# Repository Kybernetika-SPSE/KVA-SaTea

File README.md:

# KVA-SaTea
Model malé vesmírné sondy pro výuku

## Dokumentace a výrobní podklady

 - Schéma [zde](scheme.pdf)
 - Seznam součástek pro osazování - [html](bom/ibom.html), [csv](bom/BOM-SaTea.csv)
 - Archivované gerber soubory pro výrobu [zde](production/SaTea_-_small_teachy_satellite_4.zip)
 - 

## Licence

Projekt je volně šířitelný pod MIT licencí [zde](LICENSE)

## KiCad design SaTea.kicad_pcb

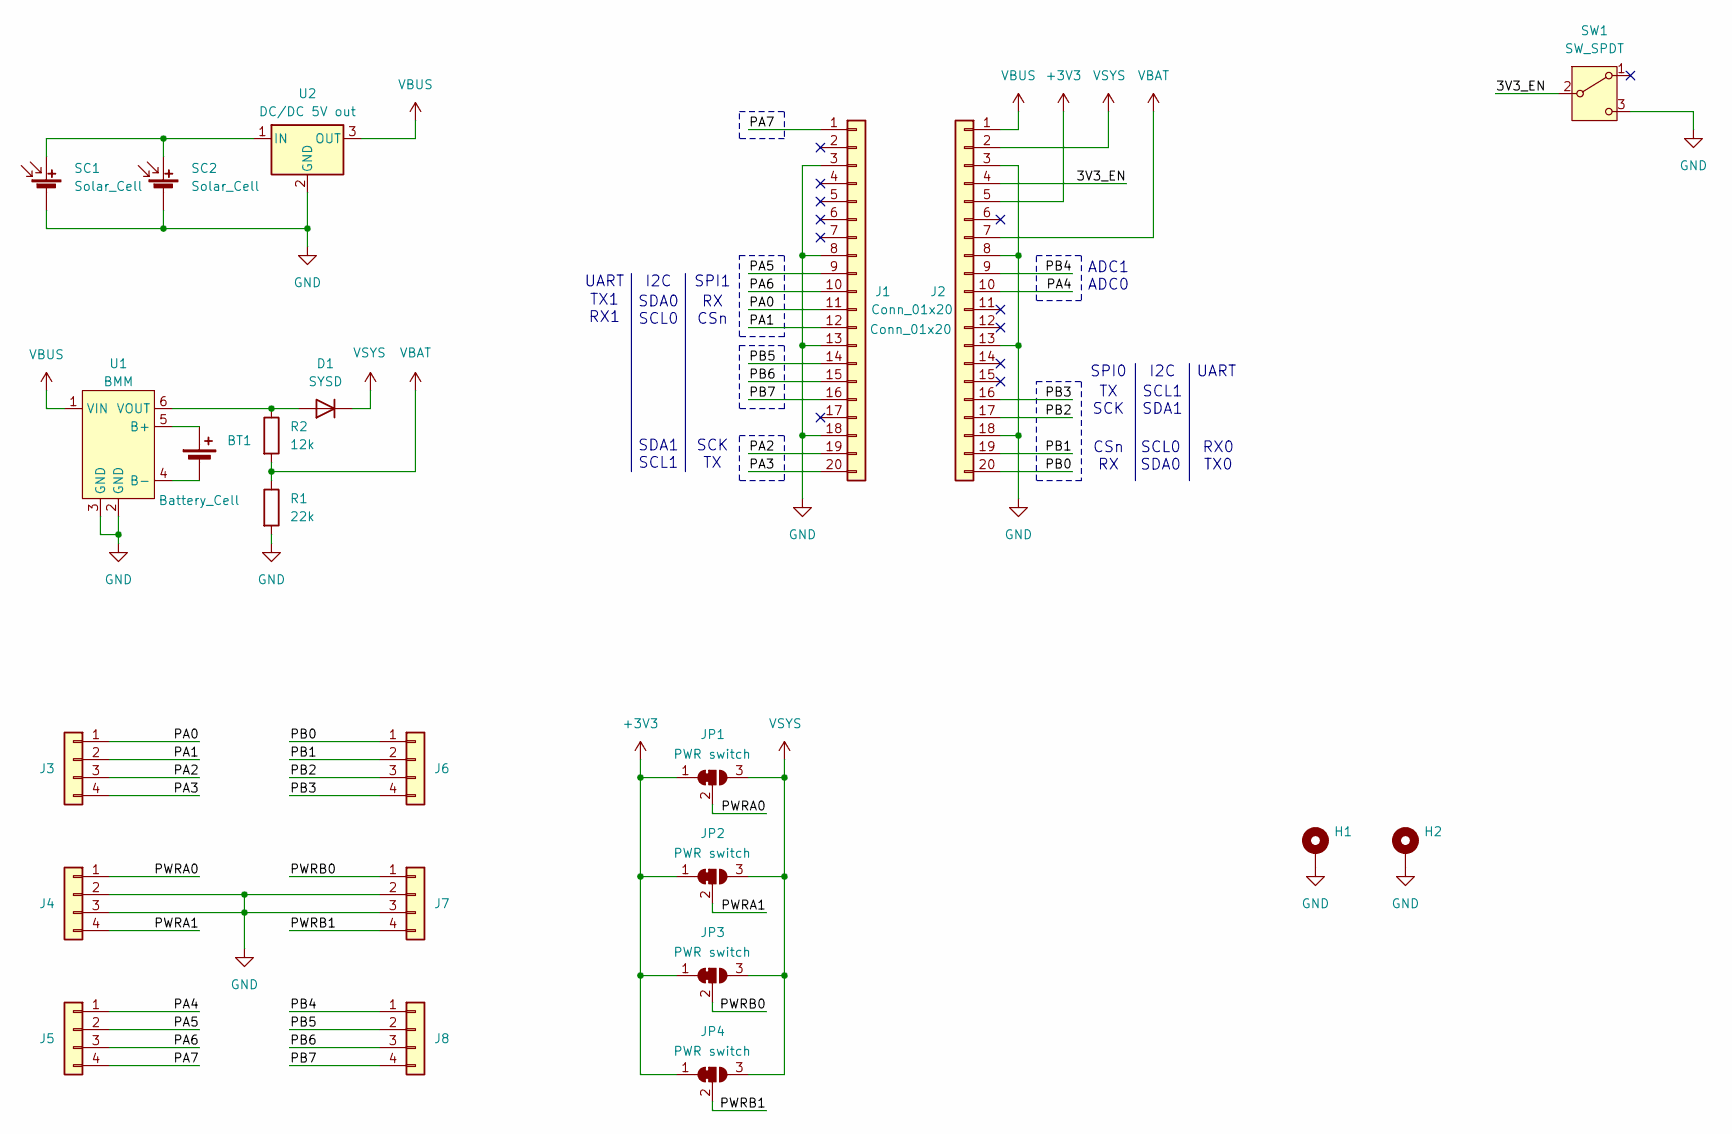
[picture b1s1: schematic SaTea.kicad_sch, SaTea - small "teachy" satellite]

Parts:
BT1: Battery_Cell; SolderWire-0.5sqmm_1x02_P4.6mm_D0.9mm_OD2.1mm
D1: SYSD; D_A-405_P10.16mm_Horizontal
H1, H2: MountingHole_Pad; MountingHole_2.2mm_M2_Pad_Via
J1, J2: Conn_01x20; PinSocket_1x20_P2.54mm_Vertical
J3, J4, J5, J6, J7, J8: Conn_01x04; PinSocket_1x04_P2.54mm_Vertical
JP1, JP2, JP3, JP4: PWR switch; SolderJumper-3_P1.3mm_Bridged12_RoundedPad1.0x1.5mm_NumberL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
R1: 22k; R_0603_1608Metric_Pad0.98x0.95mm_HandSolder
R2: 12k; R_0603_1608Metric_Pad0.98x0.95mm_HandSolder
SC1, SC2: Solar_Cell; PinHeader_1x02_P2.54mm_Vertical
SW1: SW_SPDT; PinHeader_1x03_P2.54mm_Vertical
U1: BMM; TP4056-18650
U2: DC/DC 5V out; DC-DC BOOST Convertor module

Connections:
+3V3: J2.5, JP1.1 (A), JP2.1 (A), JP3.1 (A), JP4.1 (A)
/3V3_EN: J2.4, SW1.2 (B)
/PA0: J1.11, J3.1
/PA1: J1.12, J3.2
/PA2: J1.19, J3.3
/PA3: J1.20, J3.4
/PA4: J2.10, J5.1
/PA5: J1.9, J5.2
/PA6: J1.10, J5.3
/PA7: J1.1, J5.4
/PB0: J2.20, J6.1
/PB1: J2.19, J6.2
/PB2: J2.17, J6.3
/PB3: J2.16, J6.4
/PB4: J2.9, J8.1
/PB5: J1.14, J8.2
/PB6: J1.15, J8.3
/PB7: J1.16, J8.4
/PWRA0: J4.1, JP1.2 (C)
/PWRA1: J4.4, JP2.2 (C)
/PWRB0: J7.1, JP3.2 (C)
/PWRB1: J7.4, JP4.2 (C)
GND: H1.1, H2.1, J1.3, J1.8, J1.13, J1.18, J2.3, J2.8, J2.13, J2.18, J4.2, J4.3, J7.2, J7.3, R1.2, SC1.2 (-), SC2.2 (-), SW1.3 (C), U1.2 (GND), U1.3 (GND), U2.2 (GND)
unnamed: BT1.1 (+), U1.5 (B+)
unnamed: BT1.2 (-), U1.4 (B-)
unnamed: D1.2 (A), R2.1, U1.6 (VOUT)
unnamed: SC1.1 (+), SC2.1 (+), U2.1 (IN)
VBAT: J2.7, R1.1, R2.2
VBUS: J2.1, U1.1 (VIN), U2.3 (OUT)
VSYS: D1.1 (K), J2.2, JP1.3 (B), JP2.3 (B), JP3.3 (B), JP4.3 (B)

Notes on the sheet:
SCL0 SDA0
UART
CSn RX
SDA1 SCL1
RX CSn
I2C
SCK TX
TX1 RX1
RX0 TX0
TX SCK
SDA0 SCL0
SPI0
ADC1 ADC0
SCL1 SDA1
SPI1

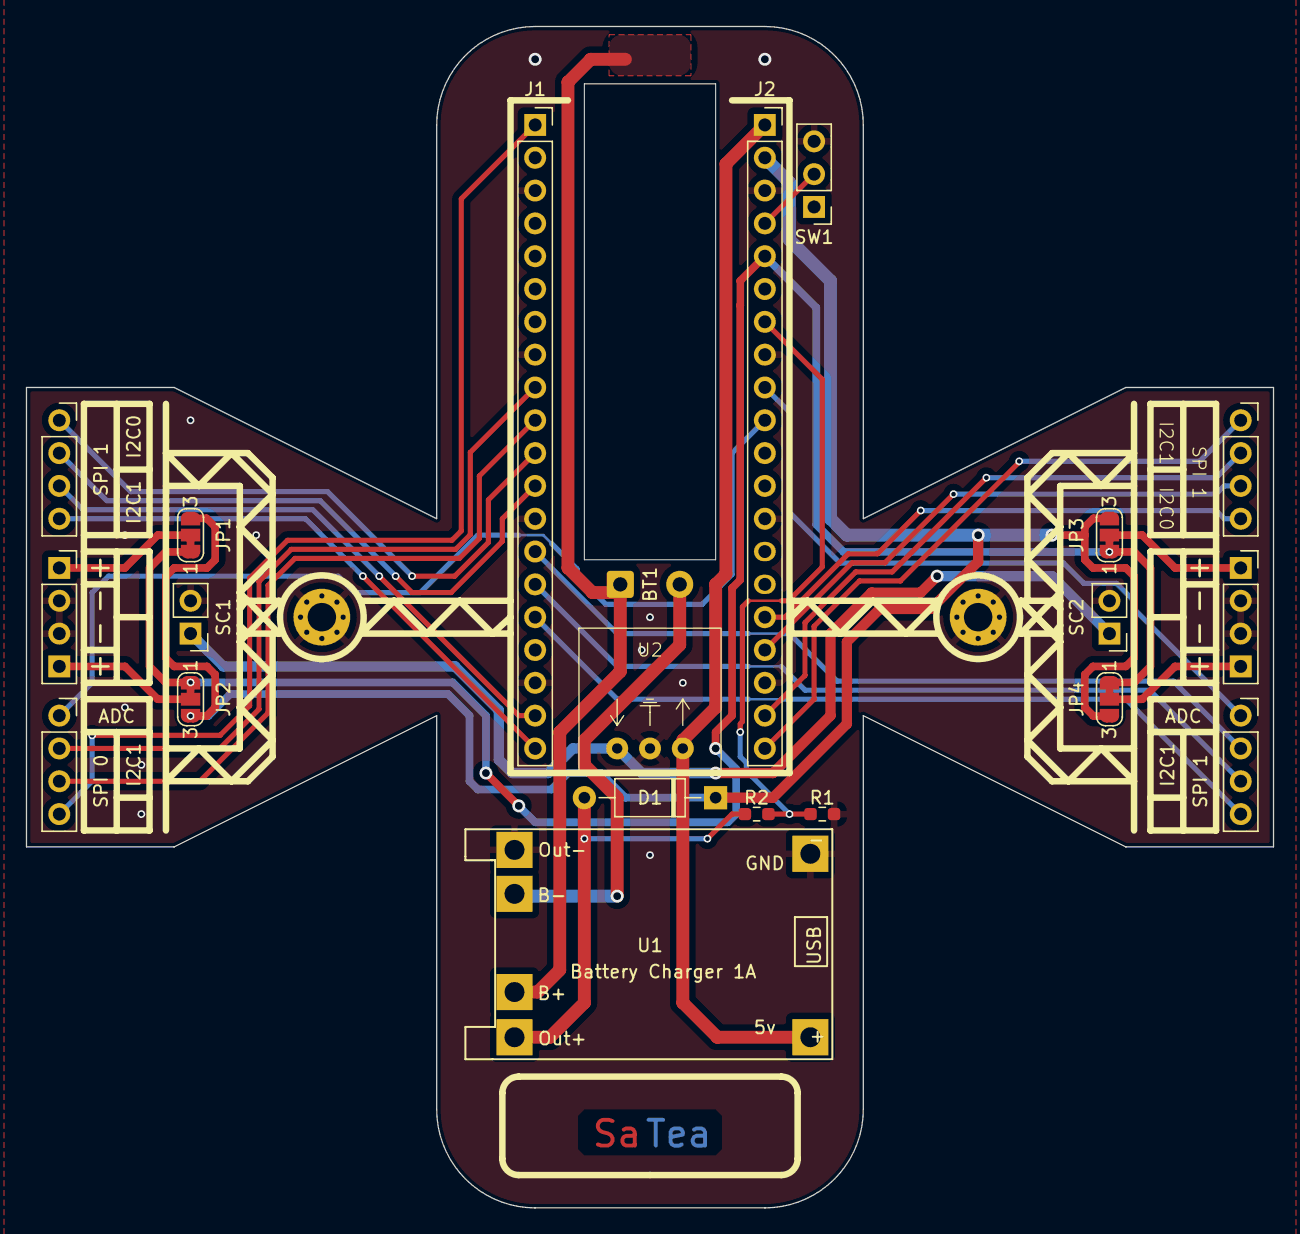
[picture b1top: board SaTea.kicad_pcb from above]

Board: 2 copper layers, 96.5 x 91.4 mm, 23 parts (0 on the bottom side), 30 nets.

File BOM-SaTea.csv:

"Reference","Value","Datasheet","Qty","DNP","Popis","Price (CZK) /pc","Supplier","Inv. number","Mnf. number"
"BT1","Battery_Cell","https://www.patlcell.com/en/product/product-414.html","1","DNP","Single-cell battery","0","Re-Use","N/A","13400"
"D1","SYSD","https://www.farnell.com/datasheets/1689669.pdf","1","","Diode","1","LCSC","C53568","1N4007RLG"
"J1,J2","Conn_01x20","https://www.lcsc.com/datasheet/lcsc_datasheet_2409302330_ZHO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","2","","Generic connector, single row, 01x20, script generated (kicad-library-utils/schlib/autogen/connector/)","2.17","Ali","N/A","N/A"
"J3,J4,J5,J6,J7,J8","Conn_01x04","~","6","DNP","Generic connector, single row, 01x04, script generated (kicad-library-utils/schlib/autogen/connector/)","0","","",""
"R1","22k","https://www.lcsc.com/datasheet/lcsc_datasheet_2304140030_YAG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","1","","Resistor","0,029","LCSC","C114065","RC0603FR-0722KL"
"R2","12k","https://www.lcsc.com/datasheet/lcsc_datasheet_2304140030_YAG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","1","","Resistor","0,024","LCSC","C137662","RC0603JR-0712KL"
"SC1,SC2","Solar_Cell","https://www.aliexpress.com/item/1005002870807425.html","2","","Single solar cell","21,53","Ali","N/A","AK68X36"
"SW1","SW_SPDT","https://www.aliexpress.com/item/1005007162182882.html","1","","Switch, single pole double throw","0,94","Ali","N/A","SS12D00"
"U1","BMM","https://www.aliexpress.com/item/1005004427739715.html","1","","TP4056+DW01A battery management module","6,28","Ali","N/A","N/A"
"U2","DC/DC 5V out","https://www.aliexpress.com/item/32809095271.html","1","","500mA Step-Down DC/DC-Regulator, 7-28V input, 5V fixed Output Voltage, LM78xx replacement, -40°C to +85°C, SIP3","7,92","Ali","N/A","N/A"

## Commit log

2024-11-14 Initial
2024-12-10 add scheme
2024-12-10 edit scheme
2024-12-10 edit scheme 2
2024-12-10 add python libs
2024-12-31 Update 31-12-24-NEZ-Final
